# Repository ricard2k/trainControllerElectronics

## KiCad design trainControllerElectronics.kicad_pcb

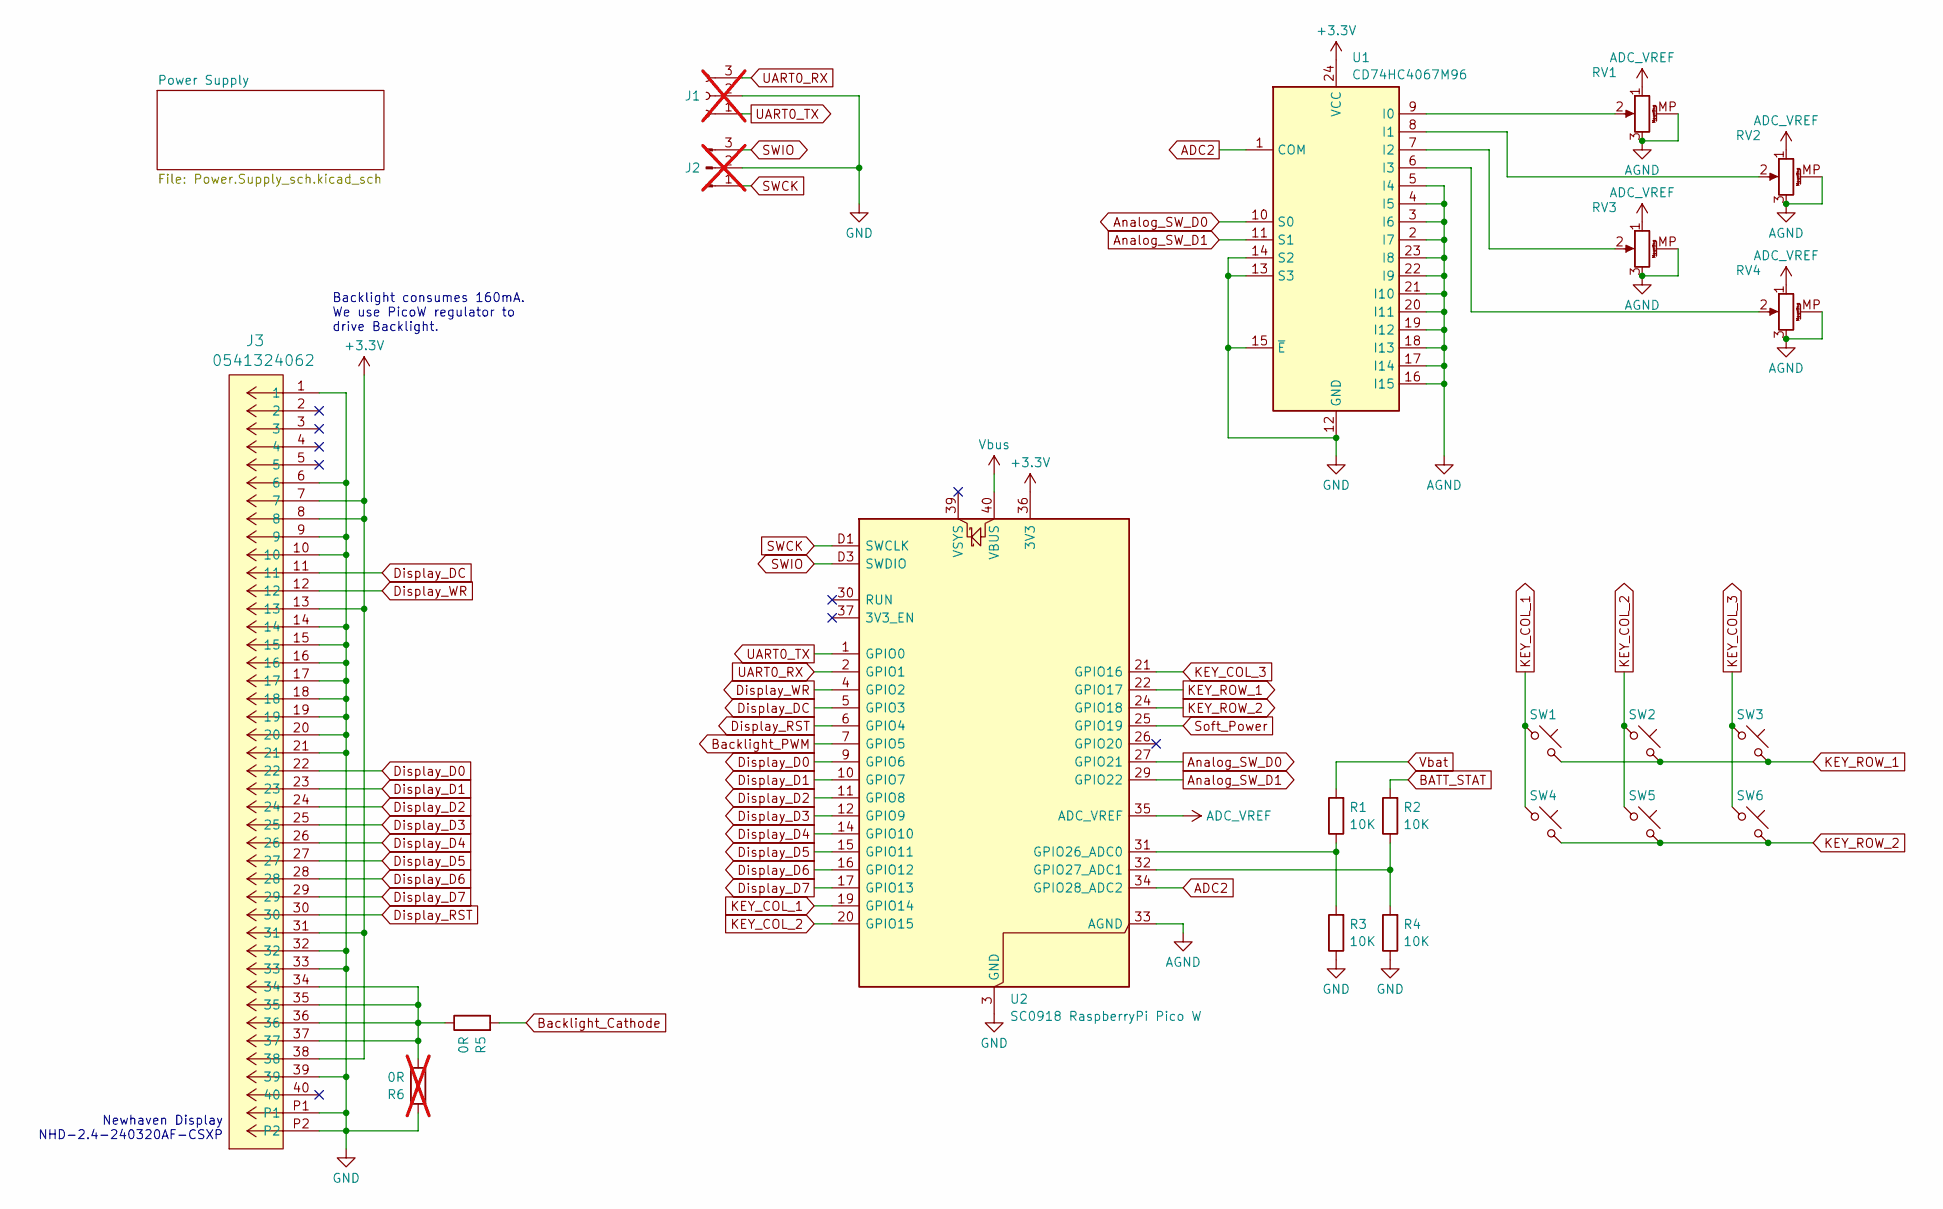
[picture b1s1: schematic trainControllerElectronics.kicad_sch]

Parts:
J1: Pin socket 2.54 1x03; PinSocket_1x03_P2.54mm_Horizontal; not fitted
J2: Pin header 2.54 1x03; PinHeader_1x03_P2.54mm_Horizontal; not fitted
J3: 0541324062; CON_541324062_MOL; Manufacturer part 0541324062; Digikey part ‎WM3436CT-ND‎
R1, R2, R3, R4: 10K; R_0805_2012Metric_Pad1.20x1.40mm_HandSolder
R5: 0R; R_0805_2012Metric_Pad1.20x1.40mm_HandSolder
R6: 0R; R_0805_2012Metric_Pad1.20x1.40mm_HandSolder; not fitted
RV1, RV2, RV3, RV4: PTV09A-4015F-B104‎; Potentiometer_Bourns_PTV09A-1_Single_Vertical; Manufacturer part PTV09A-4015F-B104‎; Digikey part PTV09A-4015F-B104-ND‎
SW1, SW2, SW3, SW4, SW5, SW6: 1825910-6; SW_PUSH_6mm; Manufacturer part 1825910-6; Digikey part 450-1650-ND
U1: CD74HC4067M96; SOIC-24W_7.5x15.4mm_P1.27mm; Manufacturer part CD74HC4067M96; Digikey part 296-29408-1-ND
U2: SC0918 RaspberryPi Pico W; RaspberryPi_Pico_W_SMD_HandSolder; Manufacturer part SC0918; Digikey part 2648-SC0918CT-ND

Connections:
+3.3V: J3.7, J3.8, J3.13, J3.31, J3.38, U1.24 (VCC), U2.36 (3V3)
ADC2: U1.1 (COM), U2.34 (GPIO28_ADC2)
ADC_VREF: RV1.1, RV2.1, RV3.1, RV4.1, U2.35 (ADC_VREF)
AGND: RV1.3, RV1.MP (MountPin), RV2.3, RV2.MP (MountPin), RV3.3, RV3.MP (MountPin), RV4.3, RV4.MP (MountPin), U1.2 (I7), U1.3 (I6), U1.4 (I5), U1.5 (I4), U1.16 (I15), U1.17 (I14), U1.18 (I13), U1.19 (I12), U1.20 (I11), U1.21 (I10), U1.22 (I9), U1.23 (I8), U2.33 (AGND)
Analog_SW_D0: U1.10 (S0), U2.27 (GPIO21)
Analog_SW_D1: U1.11 (S1), U2.29 (GPIO22)
BATT_STAT: R2.2; also elsewhere on the board
Backlight_Cathode: R5.2; also elsewhere on the board
Backlight_PWM: U2.7 (GPIO5); also elsewhere on the board
Display_D0: J3.22, U2.9 (GPIO6)
Display_D1: J3.23, U2.10 (GPIO7)
Display_D2: J3.24, U2.11 (GPIO8)
Display_D3: J3.25, U2.12 (GPIO9)
Display_D4: J3.26, U2.14 (GPIO10)
Display_D5: J3.27, U2.15 (GPIO11)
Display_D6: J3.28, U2.16 (GPIO12)
Display_D7: J3.29, U2.17 (GPIO13)
Display_DC: J3.11, U2.5 (GPIO3)
Display_RST: J3.30, U2.6 (GPIO4)
Display_WR: J3.12, U2.4 (GPIO2)
GND: J1.2, J2.2, J3.1, J3.6, J3.9, J3.10, J3.14, J3.15, J3.16, J3.17, J3.18, J3.19, J3.20, J3.21, J3.32, J3.33, J3.39, J3.P1, J3.P2, R3.1, R4.1, R6.2, U1.12 (GND), U1.13 (S3), U1.14 (S2), U1.15 (~E), U2.3 (GND), U2.8 (GND), U2.13 (GND), U2.18 (GND), U2.23 (GND), U2.28 (GND), U2.38 (GND), U2.D2 (GND); also elsewhere on the board
KEY_COL_1: SW1.1, SW4.1, U2.19 (GPIO14)
KEY_COL_2: SW2.1, SW5.1, U2.20 (GPIO15)
KEY_COL_3: SW3.1, SW6.1, U2.21 (GPIO16)
KEY_ROW_1: SW1.2, SW2.2, SW3.2, U2.22 (GPIO17)
KEY_ROW_2: SW4.2, SW5.2, SW6.2, U2.24 (GPIO18)
unnamed: J3.34, J3.35, J3.36, J3.37, R5.1, R6.1
unnamed: RV1.2, U1.9 (I0)
unnamed: RV2.2, U1.8 (I1)
unnamed: RV3.2, U1.7 (I2)
unnamed: RV4.2, U1.6 (I3)
unnamed: R1.1, R3.2, U2.31 (GPIO26_ADC0)
unnamed: R2.1, R4.2, U2.32 (GPIO27_ADC1)
SWCK: J2.1, U2.D1 (SWCLK)
SWIO: J2.3, U2.D3 (SWDIO)
Soft_Power: U2.25 (GPIO19); also elsewhere on the board
UART0_RX: J1.3, U2.2 (GPIO1)
UART0_TX: J1.1, U2.1 (GPIO0)
Vbat: R1.2; also elsewhere on the board
Vbus: U2.40 (VBUS); also elsewhere on the board

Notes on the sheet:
Backlight consumes 160mA. We use PicoW regulator to drive Backlight.
Newhaven Display NHD-2.4-240320AF-CSXP

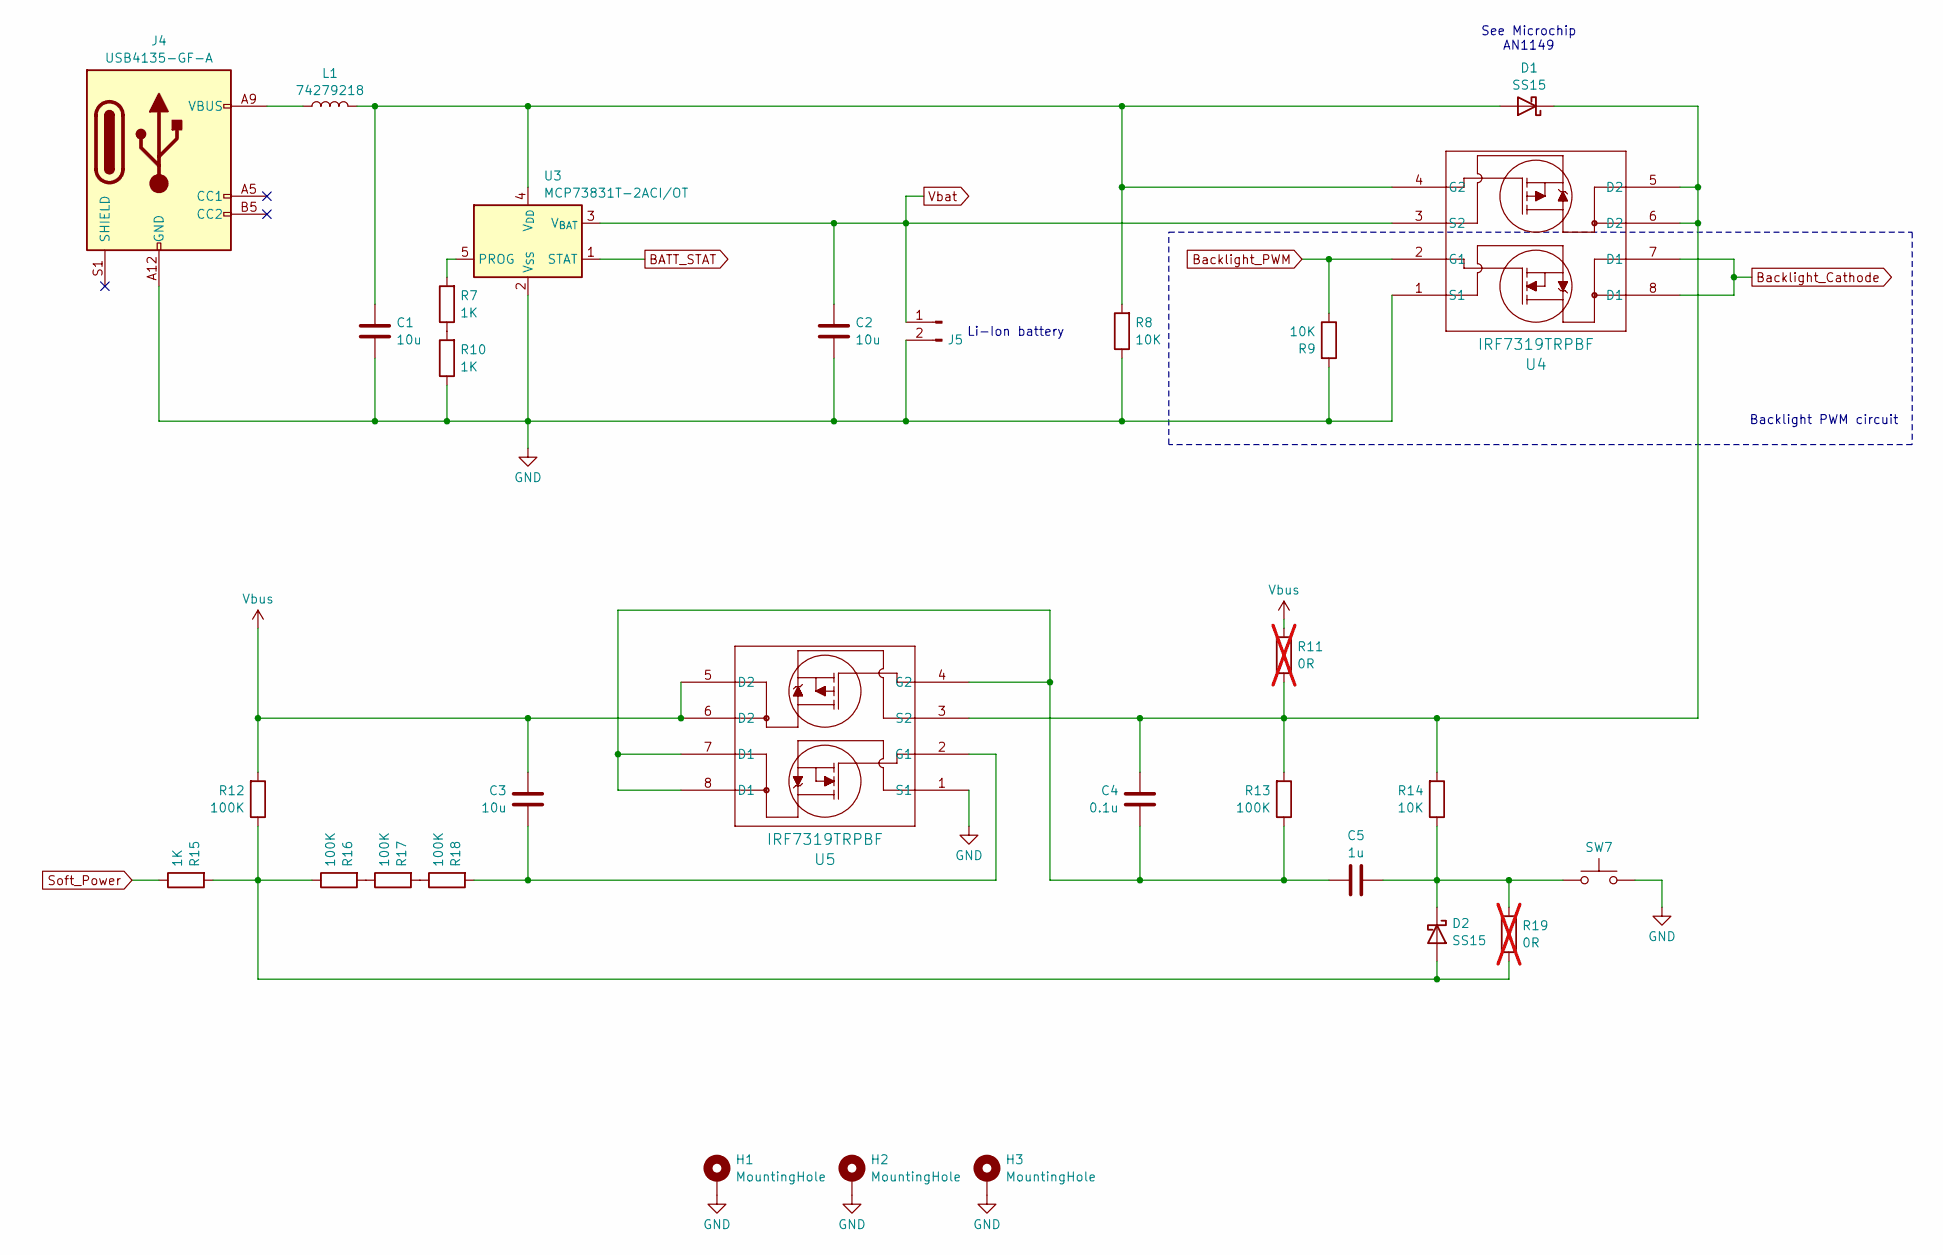
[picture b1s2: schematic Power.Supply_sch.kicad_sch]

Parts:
C1, C2, C3: 10u; C_0805_2012Metric_Pad1.18x1.45mm_HandSolder
C4: 0.1u; C_0805_2012Metric_Pad1.18x1.45mm_HandSolder
C5: 1u; C_0805_2012Metric_Pad1.18x1.45mm_HandSolder
D1, D2: SS15; D_SMA
H1, H2, H3: MountingHole; MountingHole_3.2mm_M3_Pad_Via
J4: USB4135-GF-A; USB_C_Receptacle_GCT_USB4135-GF-A_6P_TopMnt_Horizontal; Manufacturer part USB4135-GF-A; Digikey part 2073-USB4135-GF-ACT-ND
J5: B2B-PH-K-S; JST_PH_B2B-PH-K_1x02_P2.00mm_Vertical; manufacturer part B2B-PH-K-S; Digikey part 455-1704-ND
L1: 74279218; L_1206_3216Metric_Pad1.42x1.75mm_HandSolder
R7, R10, R15: 1K; R_0805_2012Metric_Pad1.20x1.40mm_HandSolder
R8, R9, R14: 10K; R_0805_2012Metric_Pad1.20x1.40mm_HandSolder
R11, R19: 0R; R_0805_2012Metric_Pad1.20x1.40mm_HandSolder; not fitted
R12, R13, R16, R17, R18: 100K; R_0805_2012Metric_Pad1.20x1.40mm_HandSolder
SW7: 1825910-6; SW_PUSH_6mm; Manufacturer part 1825910-6; Digikey part 450-1650-ND
U3: MCP73831T-2ACI/OT; SOT-23-5; Manufacturer part MCP73831T-2ACI/OT; Digikey part MCP73831T-2ACI/OTCT-ND
U4, U5: IRF7319TRPBF; TRANS_IRF7103TRPBF_INF

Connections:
BATT_STAT: U3.1 (STAT); also elsewhere on the board
Backlight_Cathode: U4.7 (D1), U4.8 (D1); also elsewhere on the board
Backlight_PWM: R9.1, U4.2 (G1); also elsewhere on the board
GND: C1.2, C2.2, H1.1, H2.1, H3.1, J4.A12 (GND), J4.B12 (GND), J5.2, R8.1, R9.2, R10.1, SW7.2, U3.2 (V_{SS}), U4.1 (S1), U5.1 (S1); also elsewhere on the board
unnamed: C1.1, D1.2 (A), L1.2, R8.2, U3.4 (V_{DD}), U4.4 (G2)
unnamed: C4.2, D1.1 (K), R11.1, R13.2, R14.2, U4.5 (D2), U4.6 (D2), U5.3 (S2)
unnamed: D2.2 (A), R12.1, R15.2, R16.1, R19.1
unnamed: C5.1, D2.1 (K), R14.1, R19.2, SW7.1
unnamed: J4.A9 (VBUS), J4.B9 (VBUS), L1.1
unnamed: R7.1, R10.2
unnamed: R16.2, R17.1
unnamed: R17.2, R18.1
unnamed: R7.2, U3.5 (PROG)
unnamed: C3.1, R18.2, U5.2 (G1)
unnamed: C4.1, C5.2, R13.1, U5.4 (G2), U5.7 (D1), U5.8 (D1)
Soft_Power: R15.1; also elsewhere on the board
Vbat: C2.1, J5.1, U3.3 (V_{BAT}), U4.3 (S2); also elsewhere on the board
Vbus: C3.2, R11.2, R12.2, U5.5 (D2), U5.6 (D2); also elsewhere on the board

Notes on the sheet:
Li-Ion battery
Backlight PWM circuit
See Microchip AN1149

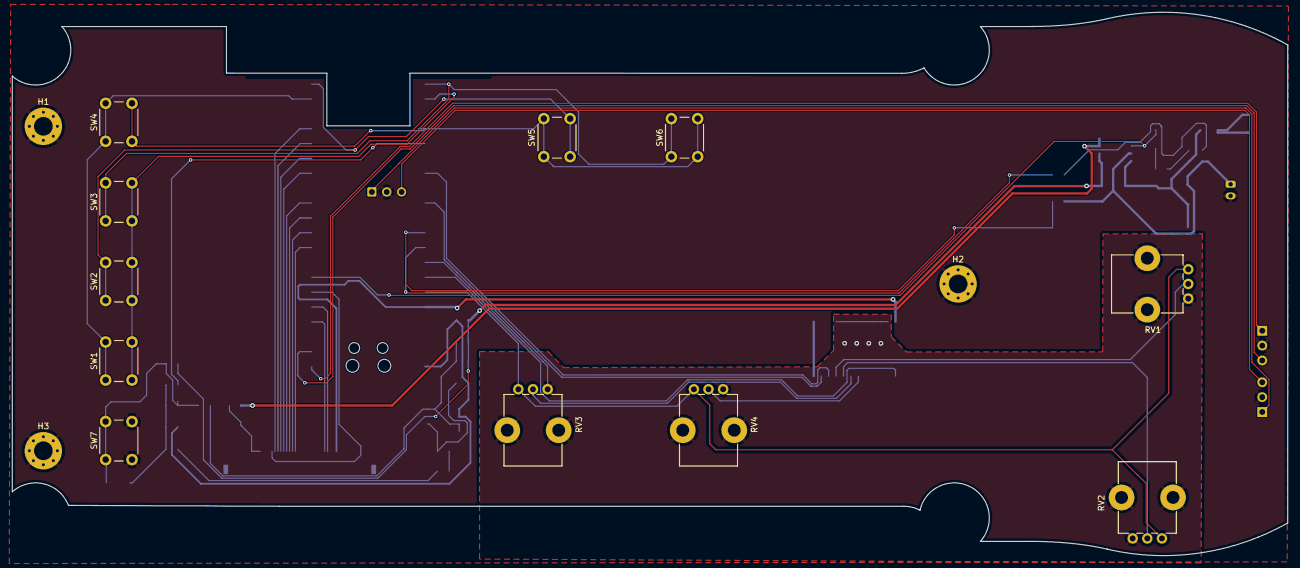
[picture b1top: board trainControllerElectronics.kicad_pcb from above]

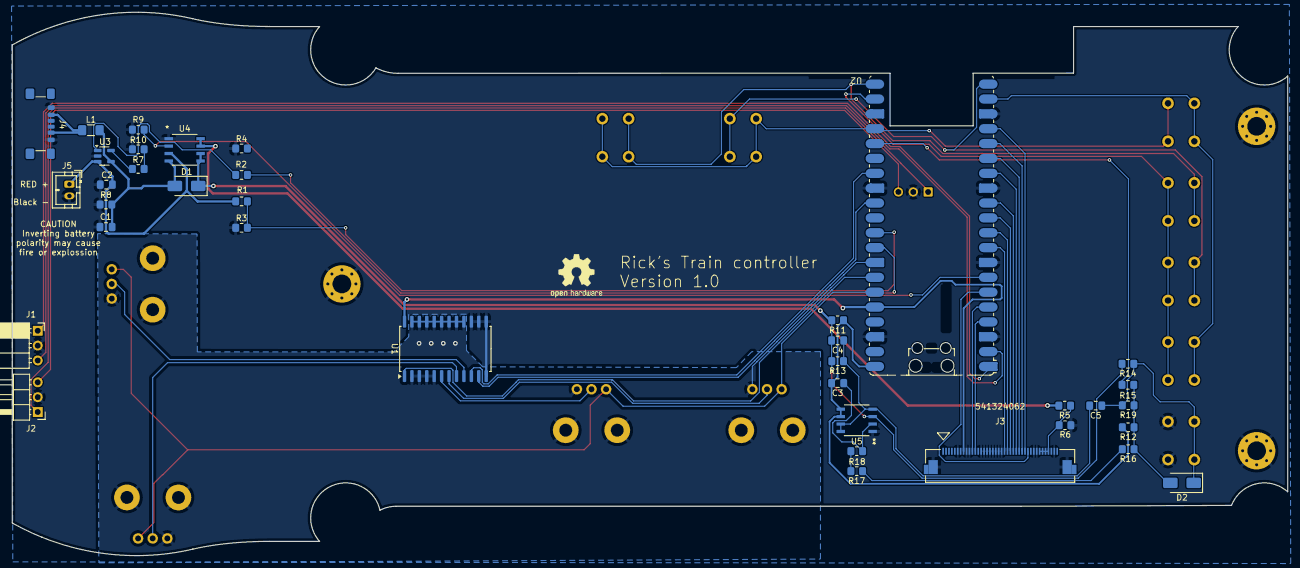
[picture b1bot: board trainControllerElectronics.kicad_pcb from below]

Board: 2 copper layers, 218.0 x 92.9 mm, 51 parts (37 on the bottom side), 51 nets.

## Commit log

2025-04-15 library cleaned
2025-04-15 New mosfet
2025-04-15 Added Battery meter
2025-05-03 PCB ready
